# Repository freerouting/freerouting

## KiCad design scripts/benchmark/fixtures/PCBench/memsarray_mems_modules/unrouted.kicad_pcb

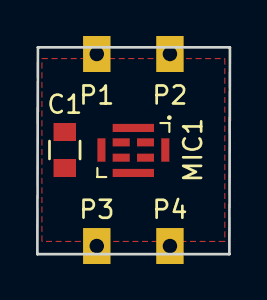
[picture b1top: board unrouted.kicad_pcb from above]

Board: 2 copper layers, 10.7 x 11.5 mm, 6 parts (0 on the bottom side), 4 nets, no tracks yet.

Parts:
C1: 1uF; C_0805
MIC1: MEMS_MIC; Mic-MEMS_Top_8_pins
P1, P2, P3, P4: CASTELLATED_PAD; Castellated_Pad

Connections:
/CLK: MIC1.3, P3.1
/OUT: MIC1.4, P4.1
DGND: C1.2, MIC1.5, P2.1
DVDD: C1.1, MIC1.1, MIC1.2, P1.1

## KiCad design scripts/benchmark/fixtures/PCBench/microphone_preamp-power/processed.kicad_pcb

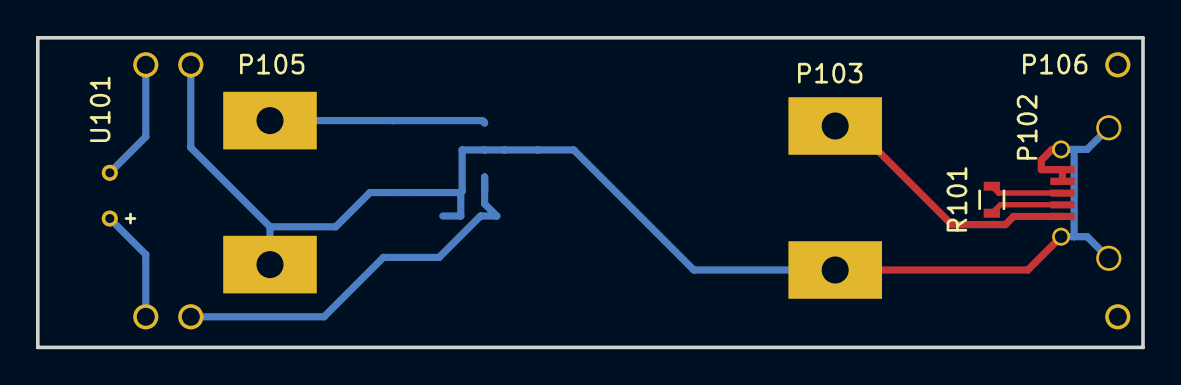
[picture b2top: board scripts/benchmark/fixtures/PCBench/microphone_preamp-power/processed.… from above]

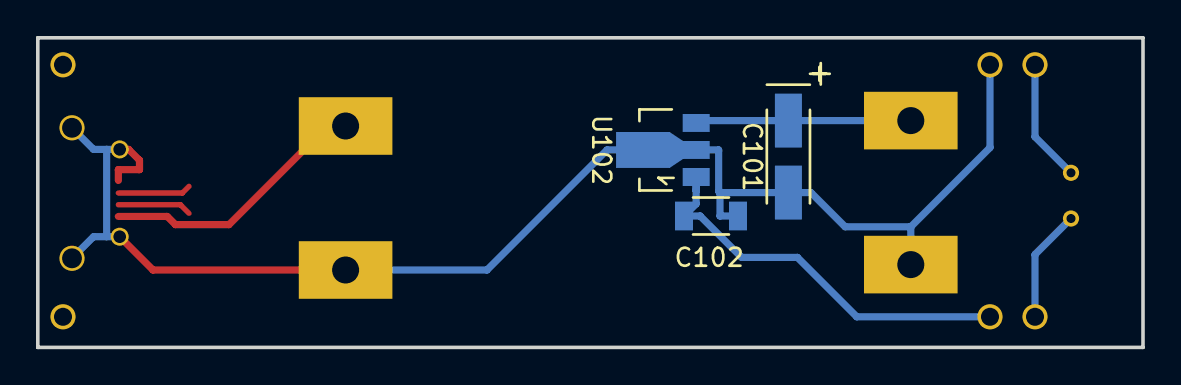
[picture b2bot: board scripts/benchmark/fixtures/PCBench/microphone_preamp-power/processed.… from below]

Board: 2 copper layers, 61.4 x 17.2 mm, 11 parts (3 on the bottom side), 8 nets.

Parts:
C101: 10u; TantalC_SizeA_EIA-3216_HandSoldering
C102: 100n; C_1206
P101, P104, P106: CONN_01X02; BOARD-CONNECT
P102: USB_OTG; USB-MICRO-B
P103, P105: CONN_01X02; BOARD-CONNECT-DCDC
R101: 0; R_0603
U101: CMIC
U102: 78L09; SOT89-3_Housing

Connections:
+12V: C101.1, P105.1, U102.3
GND: C101.2, C102.2, P102.4, P102.5, P102.6, P103.2, P104.2, P105.2, U102.2
unnamed: C102.1, P104.1, U102.1
unnamed: P101.1, U101.1
unnamed: P101.2, U101.2
unnamed: P102.1, P103.1
unnamed: P102.2, R101.1
unnamed: P102.3, R101.2

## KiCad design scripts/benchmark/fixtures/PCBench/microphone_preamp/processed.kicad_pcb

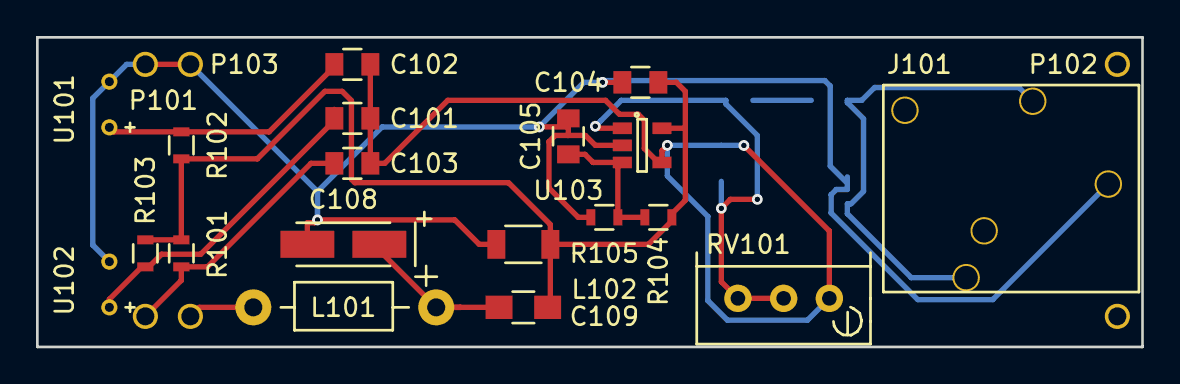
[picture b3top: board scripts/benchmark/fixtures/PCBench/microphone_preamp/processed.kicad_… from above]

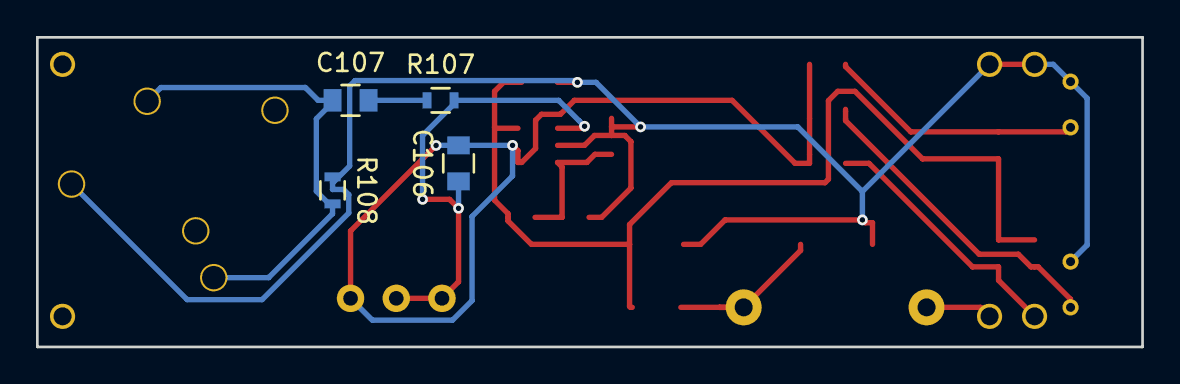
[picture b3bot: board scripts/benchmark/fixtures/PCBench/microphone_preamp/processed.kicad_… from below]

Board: 2 copper layers, 61.4 x 17.2 mm, 26 parts (4 on the bottom side), 12 nets.

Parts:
C101, C102, C103, C105, C107: 2.2u; C_0805
C104: 10n; C_0805
C106: 16p; C_0805
C108: 10u; TantalC_SizeA_EIA-3216_HandSoldering
C109: 100n; C_1206
J101: PJ-324
L101: 470uH; Choke_Horizontal_RM10mm
L102: FILTER; R_0805_HandSoldering
P101, P102, P103: CONN_01X02; BOARD-CONNECT
R101, R102, R103: 14k; R_0603
R104, R105, R108: 100k; R_0603
R107: 50; R_0603
RV101: 100k; Potentiometer_Bourns_3296W_3-8Zoll_Inline_ScrewUp
U101, U102: CMIC
U103: OPA172; SOT-23-5

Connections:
+9V: C104.2, C109.1, L102.2, R101.1, R102.1, R103.1, R104.2, U103.5
GND: C104.1, C105.2, C108.2, C109.2, J101.1, P101.1, P103.1, R105.1, R108.1, U101.2, U102.2, U103.2
unnamed: C101.1, C102.1, C103.1, C106.2, RV101.1, U103.4
unnamed: C101.2, R103.2, U102.1
unnamed: C102.2, R102.2, U101.1
unnamed: C103.2, P101.2, R101.2
unnamed: C105.1, R104.1, R105.2, U103.3
unnamed: C106.1, R107.2, RV101.2, RV101.3, U103.1
unnamed: C107.1, J101.2, J101.5, R108.2
unnamed: C107.2, R107.1
unnamed: C108.1, L101.2, L102.1
unnamed: L101.1, P103.2

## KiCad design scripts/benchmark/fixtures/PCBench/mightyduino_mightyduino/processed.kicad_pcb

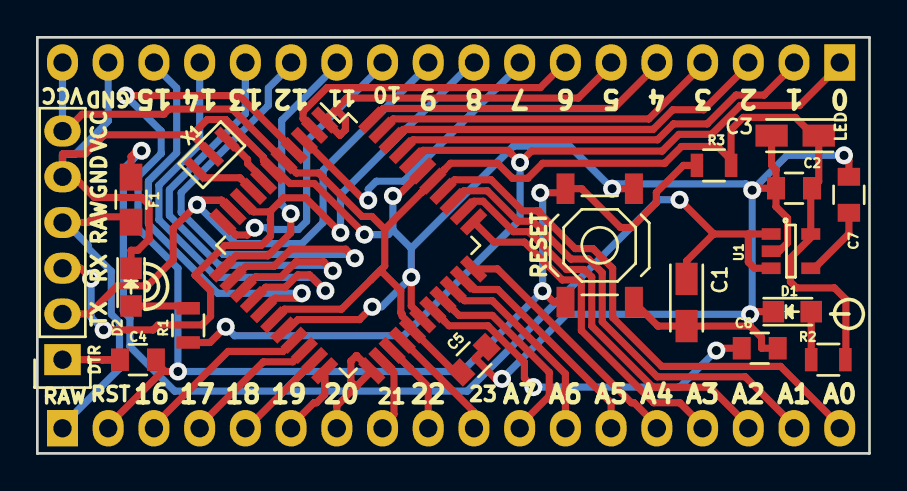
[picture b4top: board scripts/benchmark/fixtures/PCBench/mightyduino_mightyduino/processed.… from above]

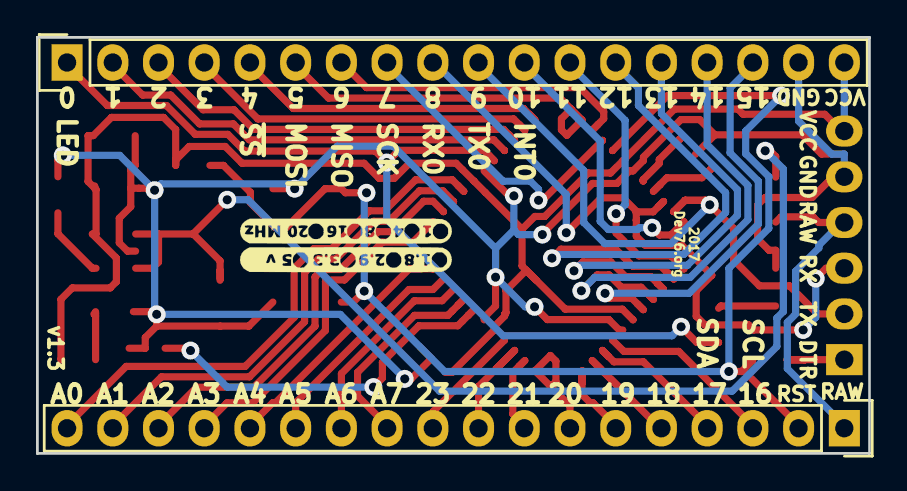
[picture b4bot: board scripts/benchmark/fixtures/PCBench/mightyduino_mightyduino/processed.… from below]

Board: 2 copper layers, 46.2 x 23.1 mm, 20 parts (2 on the bottom side), 44 nets.

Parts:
C1, C3: 10u; TantalC_SizeA_EIA-3216_Reflow
C2, C4, C5, C6: 100n; C_0805
C7: 470p; C_0805
D1: red; LED_0805
D2: blue; LED_0805
F1: 500mA; C_0805_HandSoldering
IC1: ATMEGA644P-A; LQFP-44_10x10mm_Pitch0.8mm
P1, P3: CONN_01X18; Pin_Header_Straight_1x18
P2: CONN_01X06; Pin_Header_Straight_1x06
R1, R2: 330; R_0805
R3: 10k; R_0805
SW1: RESET; SW_SPST_TL3342
U1: MIC5219-3.3YM5; SOT-23-5
X1: CSTCE 16MHZ; CSTCEv2

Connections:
/A0: IC1.37, P3.18
/A1: IC1.36, P3.17
/A2: IC1.35, P3.16
/A3: IC1.34, P3.15
/A4: IC1.33, P3.14
/A5: IC1.32, P3.13
/A6: IC1.31, P3.12
/A7: IC1.30, P3.11
/D0: IC1.40, P1.1, R1.2
/D1: IC1.41, P1.2
/D2: IC1.42, P1.3
/D3: IC1.43, P1.4
/D4: IC1.44, P1.5
/D5: IC1.1, P1.6
/D6: IC1.2, P1.7
/D7: IC1.3, P1.8
/D8: IC1.9, P1.9, P2.3
/D9: IC1.10, P1.10, P2.2
/D10: IC1.11, P1.11
/D11: IC1.12, P1.12
/D12: IC1.13, P1.13
/D13: IC1.14, P1.14
/D14: IC1.15, P1.15
/D15: IC1.16, P1.16
/D16: IC1.19, P3.3
/D17: IC1.20, P3.4
/D18: IC1.21, P3.5
/D19: IC1.22, P3.6
/D20: IC1.23, P3.7
/D21: IC1.24, P3.8
/D22: IC1.25, P3.9
/D23: IC1.26, P3.10
/DTR: C4.2, P2.1
/RAW: F1.1, P2.4, P3.1
/RESET: C4.1, IC1.4, P3.2, R3.2, SW1.2
GND: C1.2, C2.2, C3.2, C5.2, C6.2, C7.2, D1.1, D2.1, IC1.6, IC1.18, IC1.28, IC1.39, P1.17, P2.5, SW1.1, U1.2, X1.3
unnamed: C1.1, F1.2, U1.1, U1.3
unnamed: C6.1, IC1.29
unnamed: C7.1, U1.4
unnamed: D1.2, R2.1
unnamed: D2.2, R1.1
unnamed: IC1.7, X1.1
unnamed: IC1.8, X1.2
VCC: C2.1, C3.1, C5.1, IC1.5, IC1.17, IC1.27, IC1.38, P1.18, P2.6, R2.2, R3.1, U1.5
